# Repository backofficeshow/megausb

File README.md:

# megausb

PSU: https://www.ebay.co.uk/itm/DC-5V-24V-Universal-Regulated-Switching-Power-Supply-1A-60A-10W-480W-LED-3D-PSU/323575684073

USB PORT: https://www.ebay.co.uk/itm/USB-Connector-Plug-Socket-Male-Female-Type-A-B-Micro-PCB-2-0-3-0/283307836924

POLYFUSE: https://www.ebay.co.uk/itm/Polyswitch-Polyfuse-Resettable-Fuse-Radial-RXEF-RUEF-RGEF-16V-30V-60V-72V-250V/152595775446

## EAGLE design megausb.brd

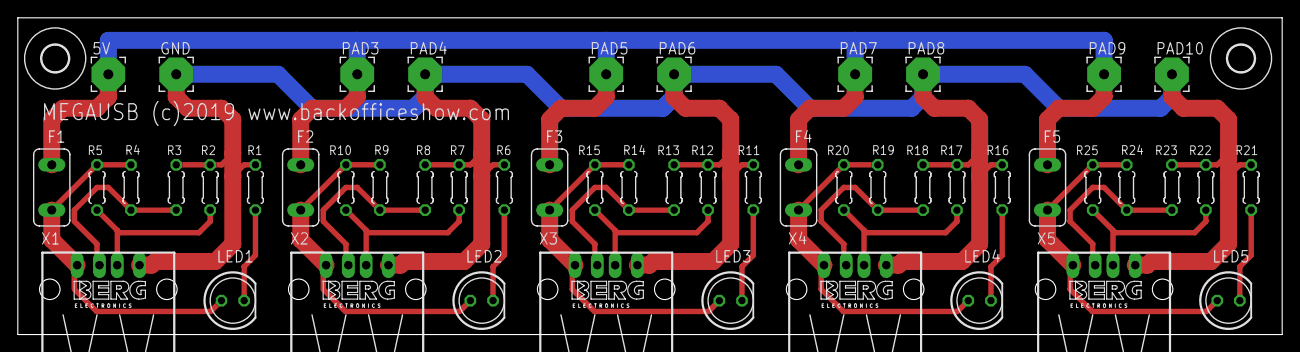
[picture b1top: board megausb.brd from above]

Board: 2 copper layers, 141.9 x 35.5 mm, 52 parts (0 on the bottom side), 22 nets.

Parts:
5V: 3,81/1,1
E$1, E$2: 3,0
F1, F2, F3, F4, F5: TE5
GND: 3,81/1,1
LED1, LED2, LED3, LED4, LED5: LED5MM
PAD3, PAD4, PAD5, PAD6, PAD7, PAD8, PAD9, PAD10: 3,81/1,1
R1, R6, R11, R16, R21: 330R; 0204/5
R2, R3, R7, R8, R12, R13, R17, R18, R22, R23: 20k; 0204/5
R4, R5, R9, R10, R14, R15, R19, R20, R24, R25: 300k; 0204/5
X1, X2, X3, X4, X5: PN87520

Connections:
5V: 5V.1, F1.2, F2.2, F3.2, F4.2, F5.2, PAD3.1, PAD5.1, PAD7.1, PAD9.1
D+: R2.1, R5.1, X1.3
D+1: R7.1, R10.1, X2.3
D+2: R12.1, R15.1, X3.3
D+3: R17.1, R20.1, X4.3
D+4: R22.1, R25.1, X5.3
D-: R3.1, R4.2, X1.2
D-1: R8.1, R9.2, X2.2
D-2: R13.1, R14.2, X3.2
D-3: R18.1, R19.2, X4.2
D-4: R23.1, R24.2, X5.2
F1-5V: F1.1, LED1.A, R4.1, R5.2, X1.1
F1-5V1: F2.1, LED2.A, R9.1, R10.2, X2.1
F1-5V2: F3.1, LED3.A, R14.1, R15.2, X3.1
F1-5V3: F4.1, LED4.A, R19.1, R20.2, X4.1
F1-5V4: F5.1, LED5.A, R24.1, R25.2, X5.1
GND: GND.1, PAD4.1, PAD6.1, PAD8.1, PAD10.1, R1.2, R2.2, R3.2, R6.2, R7.2, R8.2, R11.2, R12.2, R13.2, R16.2, R17.2, R18.2, R21.2, R22.2, R23.2, X1.4, X2.4, X3.4, X4.4, X5.4
unnamed: LED1.K, R1.1
unnamed: LED2.K, R6.1
unnamed: LED3.K, R11.1
unnamed: LED4.K, R16.1
unnamed: LED5.K, R21.1

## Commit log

2019-03-09 5 Port USB module

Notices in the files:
megausb.brd:
MEGAUSB (c)2019 www.backofficeshow.com
